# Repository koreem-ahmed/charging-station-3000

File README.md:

# charging-station-3000
## Description
This is a customed charging station which combine both funcitionablity and customed design. I personally made this project for charging my controllers while holding them in a section of my disk i also made sure to put all the games i love int he design and make the design like a customed thing to hold memories while charging my head set. i was a beginner in the 3D world but i learned a lot from onshape toturials and also i made huge project like this.

## Why it was biult
All the time i want a functionable stand to hold my things also i forget to charge me controllers and headset all the time so i came up with Charging station 3000.
It is a functionable stand which charges (type - c/micro) the controller and head sets and also could hold my phone for me on my disk. I made a custom speakers with a PAM8403 Bluetooth Dual chip to help me connect my phone to the charging station and lestin to my favorate music. also i made a custome place for TFT Screen which displays a animated valorant agents or a parts of my favorate game. I made every thing to be compatible with diffrent technieches rather than skewers also it gets its power from a plugin and a power supply which power it by 5V and 10amp. I made it cause i wanted to make a good stand and a chargin station for my controllers since i forget to charge them all the time as well as my head set and i needed something to fill my desk with and shows my love for a certain games i played and holds memory for this event (fallout). Also i didn't have speackers so i made a simple one and i want something to display animation on which was the TFT in this project.
I will usually uses it for holding and charging the controllers and my head set. Also, i will use it as a speacker and a displaying screen.

## How to use it / Build it
First of all fabricate the PCB and soleder the components then upload the code from the frimware file to the ESP32 you are using and then you should make the circiut works by using the power from the power supply you bought and connect it to were i added the silkscreen of the power source in the pcb. <br><br>
Then add the plug in and the sockets for the USB - A module and open the switch and try charging your controllers or you headset. It should work if it didn't use a multimeter to see what did you do wrong. <br><br>
If it worked you should now 3D print all the component and assemble the stand first to make it one long stand then assimple the base by glueing the pcb and the modules and the tft and the speackers to there place in the 3D design by usign the T-7000 Upgrde Glue, then add the lids of the base to it and check if it is fully inserted then put the stand you made with the x in the base and assimble them together. Now get the lid of the stand and connect it to the stand and apply glue to ensure it is stuck and dont come out and same for controllers stands after that you should apply glue for every thing and glue the led to the stand. and then open the switch again and test if it is working.

## CAD
I made the 3D desing using onshape which was like the first time from a year and also the first time working on a hard project at least for me. I had reasearch amound many sources to know how to connect parts by using a circular locks or a simple X shape to put it in the part you want to stick the stand to.
Link for the design : https://cad.onshape.com/documents/88c56ed8aab31b153241640c/w/0ef32f34aec87c837a4e1bb7/e/6c9149601bcb3d752fbc995a

### The whole design

## PCB & Schematic designing
I made a cutom PCB after searching for the components and knew that i need one for manigaing electricity and to soleder the Type-A modules in it.

### Schematic
I made the connections of the sound system, TFT, ESP32, and the charging modules
<br>

### PCB

## magazine

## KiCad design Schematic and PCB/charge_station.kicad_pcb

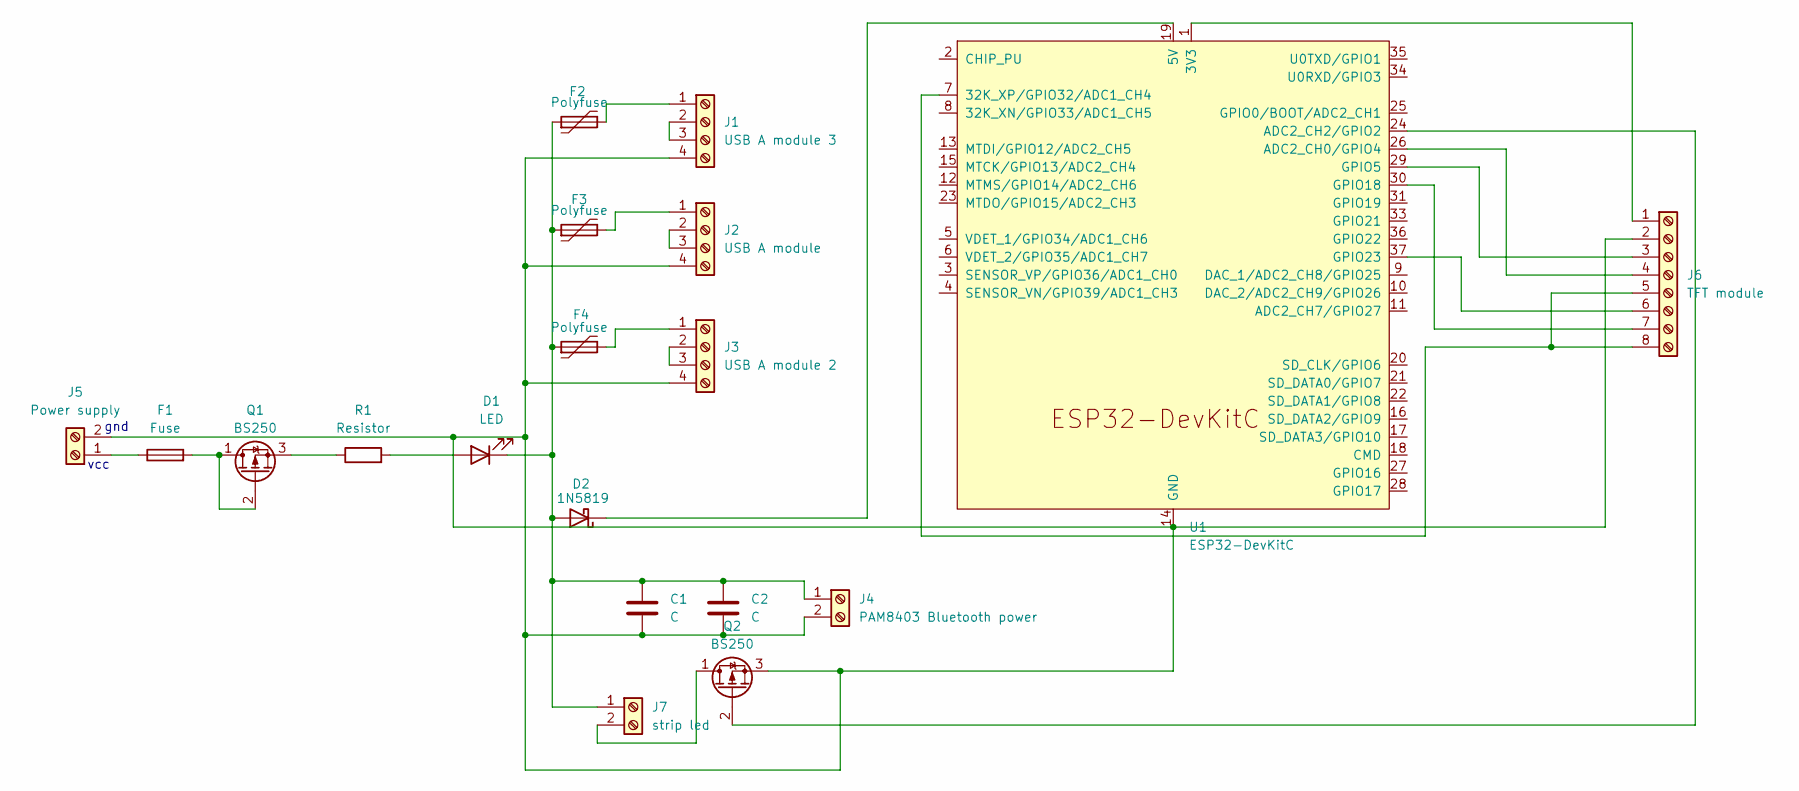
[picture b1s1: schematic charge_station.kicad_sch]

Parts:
C1: C; C_1808_4520Metric
C2: C; CP_Radial_D8.0mm_P3.80mm
D1: LED; LED_D3.0mm
D2: 1N5819; D_DO-41_SOD81_P10.16mm_Horizontal
F1: Fuse; Fuse_Littelfuse_372_D8.50mm
F2, F3, F4: Polyfuse; Fuse_Bourns_MF-RG400
J1: USB A module 3; LED_D5.0mm-4_RGB_Wide_Pins
J2: USB A module; LED_D5.0mm-4_RGB_Wide_Pins
J3: USB A module 2; LED_D5.0mm-4_RGB_Wide_Pins
J4: PAM8403 Bluetooth power; LED_D1.8mm_W1.8mm_H2.4mm_Horizontal_O1.27mm_Z8.2mm
J5: Power supply; LED_D1.8mm_W1.8mm_H2.4mm_Horizontal_O1.27mm_Z8.2mm
J6: TFT module; PinHeader_2x04_P1.00mm_Vertical
J7: strip led; LED_D1.8mm_W1.8mm_H2.4mm_Horizontal_O1.27mm_Z8.2mm
Q1, Q2: BS250; TO-92_Inline
R1: Resistor; R_Axial_DIN0207_L6.3mm_D2.5mm_P10.16mm_Horizontal
U1: ESP32-DevKitC

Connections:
unnamed: D1.2 (A), R1.2
unnamed: C1.1, C2.1, D1.1 (K), D2.2 (A), F2.1, F3.1, F4.1, J4.1, J7.1
unnamed: D2.1 (K), U1.19 (5V)
unnamed: F2.2, J1.1
unnamed: J1.2, J1.3
unnamed: C1.2, C2.2, J1.4, J2.4, J3.4, J4.2, J5.2, J6.2, Q2.3 (S), U1.14 (GND), U1.32 (GND), U1.38 (GND)
unnamed: F3.2, J2.1
unnamed: J2.2, J2.3
unnamed: F4.2, J3.1
unnamed: J3.2, J3.3
unnamed: F1.1, J5.1
unnamed: J6.1, U1.1 (3V3)
unnamed: J6.3, U1.29 (GPIO5)
unnamed: J6.4, U1.26 (ADC2_CH0/GPIO4)
unnamed: J6.5, J6.8, U1.7 (32K_XP/GPIO32/ADC1_CH4)
unnamed: J6.6, U1.37 (GPIO23)
unnamed: J6.7, U1.30 (GPIO18)
unnamed: J7.2, Q2.1 (D)
unnamed: F1.2, Q1.1 (D), Q1.2 (G)
unnamed: Q1.3 (S), R1.1
unnamed: Q2.2 (G), U1.24 (ADC2_CH2/GPIO2)

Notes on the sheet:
gnd
vcc

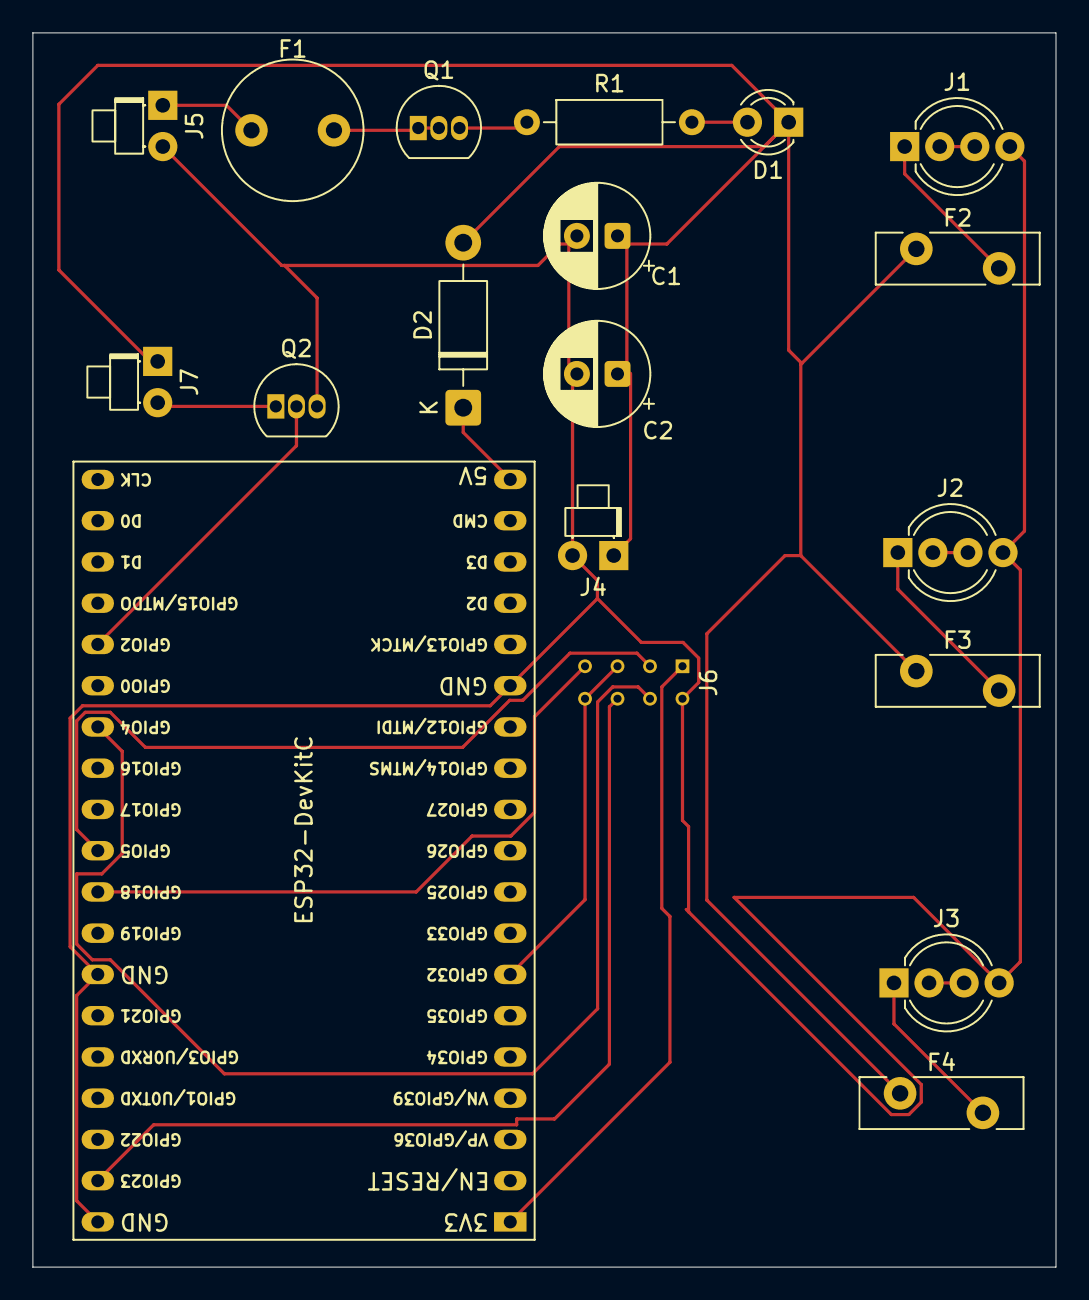
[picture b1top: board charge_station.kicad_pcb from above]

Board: 2 copper layers, 63.0 x 76.0 mm, 19 parts (0 on the bottom side), 21 nets.

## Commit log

2026-06-02 Enhance README with project details and images
    Expanded project description, detailing functionality and design process. Added sections for CAD and PCB design with images.
2026-06-02 Revise images and correct spelling errors in README
    Updated image sizes and fixed typos in the README.
2026-06-02 Fix image sizes and typos in README.md
    Updated image sizes in the CAD section and corrected spelling errors.
2026-06-02 Fix typos and enhance README content
    Corrected spelling and grammar errors in the README, improved clarity of project description, and updated section titles.
2026-06-03 Fix formatting and add hyperlink for power supply
2026-06-03 Fix formatting issues in BOM.csv
2026-06-04 Add link to CAD design in README
    Added a link to the CAD design for better accessibility.
2026-06-04 Fix design link in README
    Updated the link for the design in the CAD section of the README.
2026-06-04 Update README with corrected link and typos
    Fixed link formatting and corrected typos in the README.
2026-06-04 Fix link formatting in README.md
    Corrected the link formatting in the README.
2026-06-04 Fix link formatting in README.md
    Corrected the formatting of the link to the design in the CAD section.
2026-06-04 Revise README for clarity and correctness
    Corrected spelling and grammatical errors, improved clarity and structure in the README file. Added a section on how to use and build the charging station.
2026-06-05 Update speaker glue link in BOM.csv
    Updated the link for speaker glue to a specific product page.
2026-06-05 Revise README for clarity and grammar improvements
    Corrected spelling and grammatical errors, improved clarity of instructions, and added details for building and using the charging stand.
2026-06-05 Refactor usage instructions in README.md
    Removed duplicate instructions and improved clarity in the usage section.
2026-06-05 Fix typos and enhance assembly instructions in README
    Corrected typos and improved clarity in instructions for assembling the charging station.
